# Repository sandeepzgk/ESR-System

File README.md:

## Electrical Stochastic Resonance (ESR) System : Source Code

This repository hosts the full source for an end‑to‑end ESR system:
- A web‑based RC circuit analyzer (Simulator)
- MicroPython firmware for a Pico W/2W audio device (Firmware)
- A KiCad hardware design for the device (PCB)
- A local experiment runner for ABX/QUEST studies (ABXTester)

Hosted analyzer (no install): https://sandeepzgk.github.io/ESR-System/

### Quick links
- Simulator (web analyzer): Simulator/README.md : hosted at https://sandeepzgk.github.io/ESR-System/
- Firmware (Pico W/2W): Firmware/README.md
- PCB (sr‑device KiCad): PCB/README.md
- ABXTester (experiment runner): ABXTester/readme.md

### Repository structure
- Simulator/ : React + TypeScript single‑page app for ESR RC analysis (sine and noise modes), Tailwind UI, GitHub Pages deploy
- Firmware/ : MicroPython code for Wi‑Fi control and I2S audio playback (HTTP endpoints: play/gain/led/status), Q15 volume scaling
- PCB/ : KiCad project (schematic/PCB), repo‑local libraries and production outputs (v1, v2); JLC importer utility
- ABXTester/ : Flask‑based local runner for experiments (QUEST thresholding + ABX trials), CSV/JSON results

### Citations

#### APA
Kollannur, S., Zhao, F., Chen, Y., & Culbertson, H. (2025). Electrical Stochastic Resonance (ESR) System [Computer software]. GitHub. https://github.com/sandeepzgk/ESR-System

#### MLA
Kollannur, S., Zhao, F., Chen, Y., and Culbertson, H. Electrical Stochastic Resonance (ESR) System. 2025. GitHub, https://github.com/sandeepzgk/ESR-System.

#### Chicago
Kollannur, S., F. Zhao, Y. Chen, and H. Culbertson. 2025. Electrical Stochastic Resonance (ESR) System. GitHub repository. https://github.com/sandeepzgk/ESR-System.

#### BibTeX
```bibtex
@software{esr_system_2025,
  author    = {Kollannur, S. and Zhao, F. and Chen, Y. and Culbertson, H.},
  title     = {Electrical Stochastic Resonance (ESR) System},
  year      = {2025},
  publisher = {GitHub},
  url       = {https://github.com/sandeepzgk/ESR-System},
  note      = {A system for electrical stochastic resonance research including circuit analysis, firmware, hardware design, and experiment tools}
}
```

#### Software Citation Format
Kollannur, S., Zhao, F., Chen, Y., & Culbertson, H. (2025). Electrical Stochastic Resonance (ESR) System [Source code]. GitHub. https://github.com/sandeepzgk/ESR-System : A system for electrical stochastic resonance research including circuit analysis, firmware, hardware design, and experiment tools.

### Brief technical summary
- Web analyzer: React 18 + TypeScript, Tailwind; static SPA deployable to GitHub Pages
- Firmware: MicroPython on RP2040 (Pico W/2W), machine.I2S TX, HTTP API over Wi‑Fi
- Hardware: KiCad project with pinned repo‑local symbol/footprint/3D libraries; production files for fabrication
- Experiments: Python (Flask) with two‑channel audio playback, CSV/JSON logging, QUEST thresholding

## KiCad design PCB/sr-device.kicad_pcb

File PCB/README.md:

## PCB SR Device KiCad Project

### 1) Overview
KiCad project for the ESR hardware: a Pico‑based audio playback/amp board ("sr-device"). Includes:
- KiCad schematic, PCB, and project files (sr-device.kicad_*)
- Curated symbol/footprint/3D libraries under PCB/lib for key parts (DAC, amplifier, regulators, passives, connectors)
- Production outputs under PCB/production/v1 and v2 (BOM, positions, designators, zipped fab packages)
- jlcimporter.py utility to generate and normalize part libraries using JLC2KiCadLib

Notable parts
- DAC: PCM5100A
- Amplifier: TPA3112D1
- Regulators: LM78M05C, LM7812S, LM1085IS-12, AP7333-33
- Inductors/caps/resistors; Pico headers/footprints; custom logos

### 2) How to open / produce outputs
Open in KiCad 7/8
- Open PCB/sr-device.kicad_pro; KiCad will resolve sym-lib-table and fp-lib-table to PCB/lib/*

Generate fabrication
- Use KiCad’s Plot and Fabrication Toolkit (options in fabrication-toolkit-options.json)
- Export Gerbers, drill files, position files, and BOM as needed

JLC integration workflow
- jlcimporter.py wraps JLC2KiCadLib to create per‑part libraries under PCB/lib/<MFR_PART>/
- It normalizes filenames (symbol.kicad_sym, footprint.kicad_mod, model.step) and updates lib tables
- Run from PCB/: python jlcimporter.py --lcsc_part_numbers C12345 C67890

### 3) Where it has been tested
- Designed and opened in KiCad; produced v1 and v2 outputs in PCB/production
- Libraries resolved via sym-lib-table and fp-lib-table within this project (KIPRJMOD relative paths)

### 4) History and rationale (commit highlights)
- 79621ca (PCB): Initial KiCad project checked in with curated libraries and production artifacts (v1, v2)
- Custom library structure chosen for reproducibility and to avoid external dependency drift; jlcimporter.py automates bringing JLC parts into repo‑local libs

Design choices
- Repo‑local symbol/footprint/3D models for repeatable builds and offline use
- KIPRJMOD‑relative paths in lib tables so the project remains portable
- Versioned production output directories to track released fab packages

### 5) Brief technical summary
- EDA: KiCad project with sym/fp tables pinned to PCB/lib
- Manufacturing: BOM/pos/designator exports for JLC; STEP models included for 3D
- Utilities: Python importer normalizes JLC outputs and patches lib tables

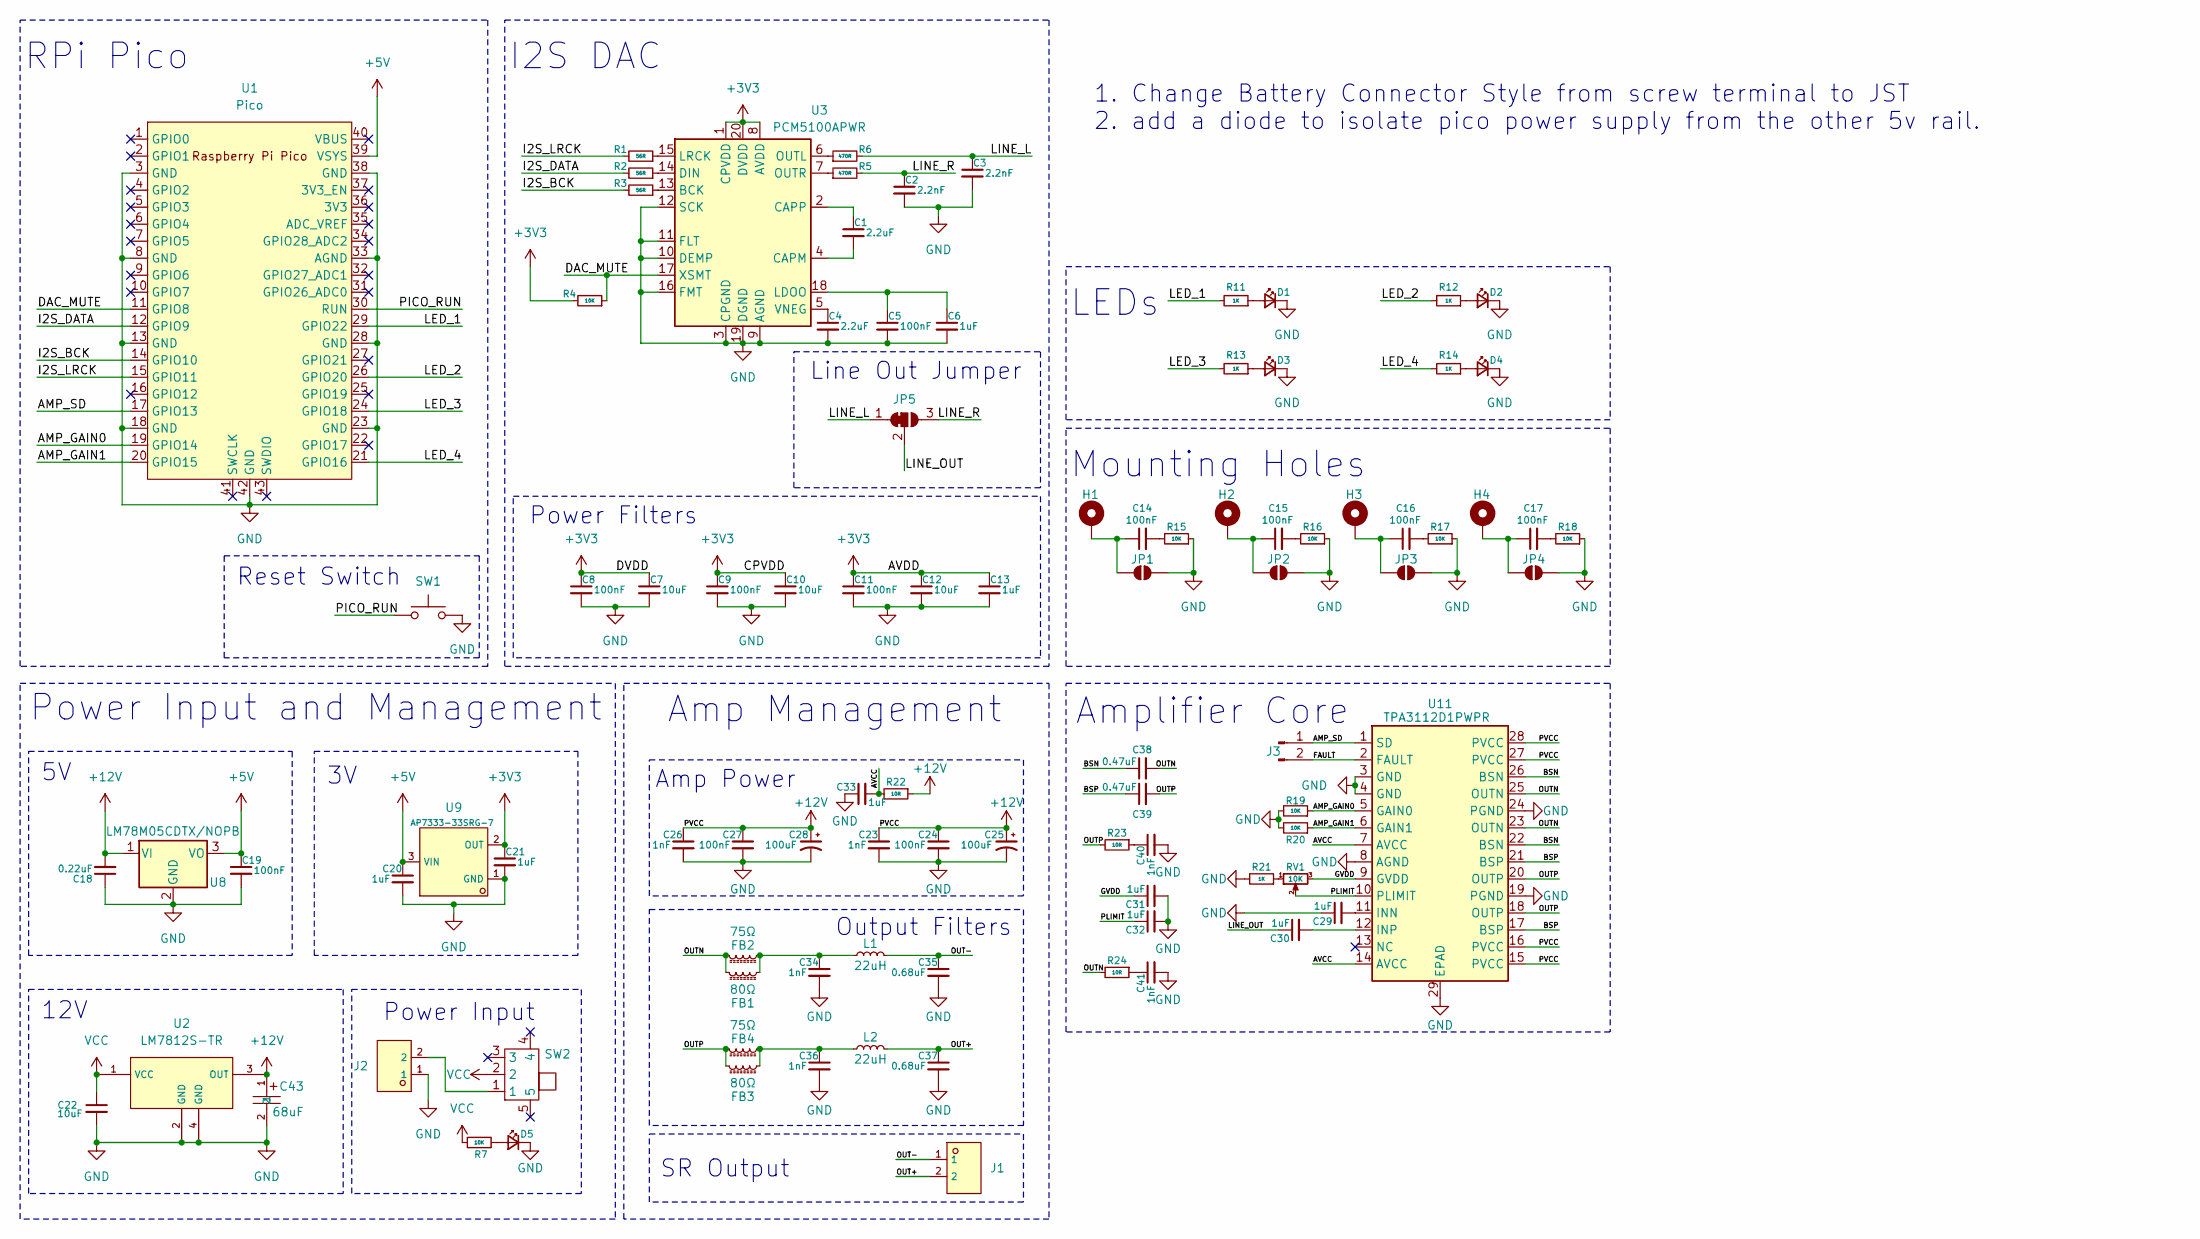
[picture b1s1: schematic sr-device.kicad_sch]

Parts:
C1, C4: 2.2uF; C_0603_1608Metric; LCSC C57895
C2, C3: 2.2nF; C_0603_1608Metric; LCSC C2835509
C5, C8, C9, C11, C14, C15, C16, C17, C19, C24, C27: 100nF; C_0603_1608Metric; LCSC C88219
C6, C13, C20, C21, C29, C30, C31, C32, C33: 1uF; C_0603_1608Metric; LCSC C841050
C7, C10, C12, C22: 10uF; C_0603_1608Metric; LCSC C386081
C18: 0.22uF; C_0603_1608Metric; LCSC C107083
C23, C26, C34, C36, C40, C41: 1nF; C_0603_1608Metric; LCSC C340644
C25, C28: 100uF; CP_Elec_6.3x5.4; LCSC C2887272
C35, C37: 0.68uF; C_0603_1608Metric; LCSC C694504
C38, C39: 0.47uF; C_0603_1608Metric; LCSC C162281
C43: 68uF; footprint; LCSC C7220
D1, D2, D3, D4, D5: LED_Small; LED_0603_1608Metric; LCSC C89811
FB1, FB3: 80Ω; L_0805_2012Metric; LCSC C2971887
FB2, FB4: 75Ω; L_1806_4516Metric; LCSC C14586
H1, H2, H3, H4: MountingHole; MountingHole_3.2mm_M3_ISO7380_Pad
J1, J2: KF301-5_0-2P; footprint; LCSC C474881
J3: Conn_01x02_Pin; PinHeader_1x02_P2.54mm_Vertical; LCSC DNP
JP1, JP2, JP3, JP4: SolderJumper_2_Open; SolderJumper-2_P1.3mm_Open_TrianglePad1.0x1.5mm
JP5: SolderJumper_3_Bridged12; SolderJumper-3_P1.3mm_Bridged12_RoundedPad1.0x1.5mm
L1, L2: 22uH; footprint; LCSC C845053
R1, R2, R3: 56R; R_0603_1608Metric; LCSC C227967
R4, R7, R15, R16, R17, R18, R19, R20: 10K; R_0603_1608Metric; LCSC C465463
R5, R6: 470R; R_0603_1608Metric; LCSC C114669
R11, R12, R13, R14, R21: 1K; R_0603_1608Metric; LCSC C73797
R22, R23, R24: 10R; R_0603_1608Metric; LCSC C441910
RV1: 10K; footprint; LCSC C515300
SW1: PTS636SK25SMTRLFS; footprint; LCSC C2689642
SW2: SS-12D11L7; LCSC C2884775
U1: Pico; RPi_Pico_SMD_TH
U2: LM7812S-TR; footprint; LCSC C507140
U3: PCM5100APWR; TSSOP-20_4.4x6.5mm_P0.65mm; LCSC C131154
U8: LM78M05CDTX/NOPB; footprint; LCSC C544492
U9: AP7333-33SRG-7; footprint; LCSC C150745
U11: TPA3112D1PWPR; footprint; LCSC C133544

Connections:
+3V3: C7.1, C8.1, C9.1, C10.1, C11.1, C12.1, C13.1, C21.1, R4.2, U3.1 (CPVDD), U3.8 (AVDD), U3.20 (DVDD), U9.2 (OUT)
+5V: C19.1, C20.1, U1.39 (VSYS), U8.3 (VO), U9.3 (VIN)
+12V: C18.2, C23.1, C24.1, C25.1, C26.1, C27.1, C28.1, C43.1, R22.1, U2.3 (OUT), U8.1 (VI), U11.15 (PVCC), U11.16 (PVCC), U11.27 (PVCC), U11.28 (PVCC)
/AMP_GAIN0: R19.1, U1.19 (GPIO14), U11.5 (GAIN0)
/AMP_GAIN1: R20.1, U1.20 (GPIO15), U11.6 (GAIN1)
/AMP_SD: J3.1, U1.17 (GPIO13), U11.1 (SD)
/AVCC: C33.2, R22.2, U11.7 (AVCC), U11.14 (AVCC)
/BSN: C38.1, U11.22 (BSN), U11.26 (BSN)
/BSP: C39.1, U11.17 (BSP), U11.21 (BSP)
/DAC_MUTE: R4.1, U1.11 (GPIO8), U3.17 (XSMT)
/FAULT: J3.2, U11.2 (FAULT)
/GVDD: C31.1, RV1.3, U11.9 (GVDD)
/I2S_BCK: R3.2, U1.14 (GPIO10)
/I2S_DATA: R2.2, U1.12 (GPIO9)
/I2S_LRCK: R1.2, U1.15 (GPIO11)
/LED_1: R11.2, U1.29 (GPIO22)
/LED_2: R12.2, U1.26 (GPIO20)
/LED_3: R13.2, U1.24 (GPIO18)
/LED_4: R14.2, U1.21 (GPIO16)
/LINE_L: C3.1, JP5.1 (A), R6.2
/LINE_OUT: C30.1, JP5.2 (C)
/LINE_R: C2.1, JP5.3 (B), R5.2
/OUT+: C37.1, J1.2, L2.1
/OUT-: C35.1, J1.1, L1.1
/OUTN: C38.2, FB1.2, FB2.2, R24.2, U11.23 (OUTN), U11.25 (OUTN)
/OUTP: C39.2, FB3.2, FB4.2, R23.2, U11.18 (OUTP), U11.20 (OUTP)
/PICO_RUN: SW1.1, U1.30 (RUN)
/PLIMIT: C32.1, RV1.2, U11.10 (PLIMIT)
GND: C2.2, C3.2, C4.2, C5.2, C6.2, C7.2, C8.2, C9.2, C10.2, C11.2, C12.2, C13.2, C18.1, C19.2, C20.2, C21.2, C22.2, C23.2, C24.2, C25.2, C26.2, C27.2, C28.2, C29.1, C31.2, C32.2, C33.1, C34.2, C35.2, C36.2, C37.2, C40.2, C41.2, C43.2, D1.1 (K), D2.1 (K), D3.1 (K), D4.1 (K), D5.1 (K), J2.1, JP1.2 (B), JP2.2 (B), JP3.2 (B), JP4.2 (B), R15.1, R16.1, R17.1, R18.1, R19.2, R20.2, R21.2, SW1.2, U1.3 (GND), U1.8 (GND), U1.13 (GND), U1.18 (GND), U1.23 (GND), U1.28 (GND), U1.33 (AGND), U1.38 (GND), U1.42 (GND), U2.2 (GND), U2.4 (GND), U3.3 (CPGND), U3.9 (AGND), U3.10 (DEMP), U3.11 (FLT), U3.12 (SCK), U3.16 (FMT), U3.19 (DGND), U8.2 (GND), U9.1 (GND), U11.3 (GND), U11.4 (GND), U11.8 (AGND), U11.19 (PGND), U11.24 (PGND), U11.29 (EPAD)
unnamed: C14.2, R15.2
unnamed: C15.2, R16.2
unnamed: C16.2, R17.2
unnamed: C17.2, R18.2
unnamed: C34.1, FB1.1, FB2.1, L1.2
unnamed: C36.1, FB3.1, FB4.1, L2.2
unnamed: C40.1, R23.1
unnamed: C41.1, R24.1
unnamed: D1.2 (A), R11.1
unnamed: D2.2 (A), R12.1
unnamed: D3.2 (A), R13.1
unnamed: D4.2 (A), R14.1
unnamed: D5.2 (A), R7.1
unnamed: J2.2, SW2.1
unnamed: C14.1, H1.1, JP1.1 (A)
unnamed: C15.1, H2.1, JP2.1 (A)
unnamed: C16.1, H3.1, JP3.1 (A)
unnamed: C17.1, H4.1, JP4.1 (A)
unnamed: R21.1, RV1.1
unnamed: R3.1, U3.13 (BCK)
unnamed: C1.2, U3.4 (CAPM)
unnamed: C1.1, U3.2 (CAPP)
unnamed: R2.1, U3.14 (DIN)
unnamed: C5.1, C6.1, U3.18 (LDOO)
unnamed: R1.1, U3.15 (LRCK)
unnamed: R6.1, U3.6 (OUTL)
unnamed: R5.1, U3.7 (OUTR)
unnamed: C4.1, U3.5 (VNEG)
unnamed: C29.2, U11.11 (INN)
unnamed: C30.2, U11.12 (INP)
VCC: C22.1, R7.2, SW2.2, U2.1 (VCC)

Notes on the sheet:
Mounting Holes
RPi Pico
Power Filters
1. Change Battery Connector Style from screw terminal to JST 2. add a diode to isolate pico power supply from the other 5v rail.
Power Input and Management
LEDs
Amp Management
SR Output
Output Filters
I2S DAC
Line Out Jumper
Reset Switch
Amplifier Core
12V
Amp Power
Power Input

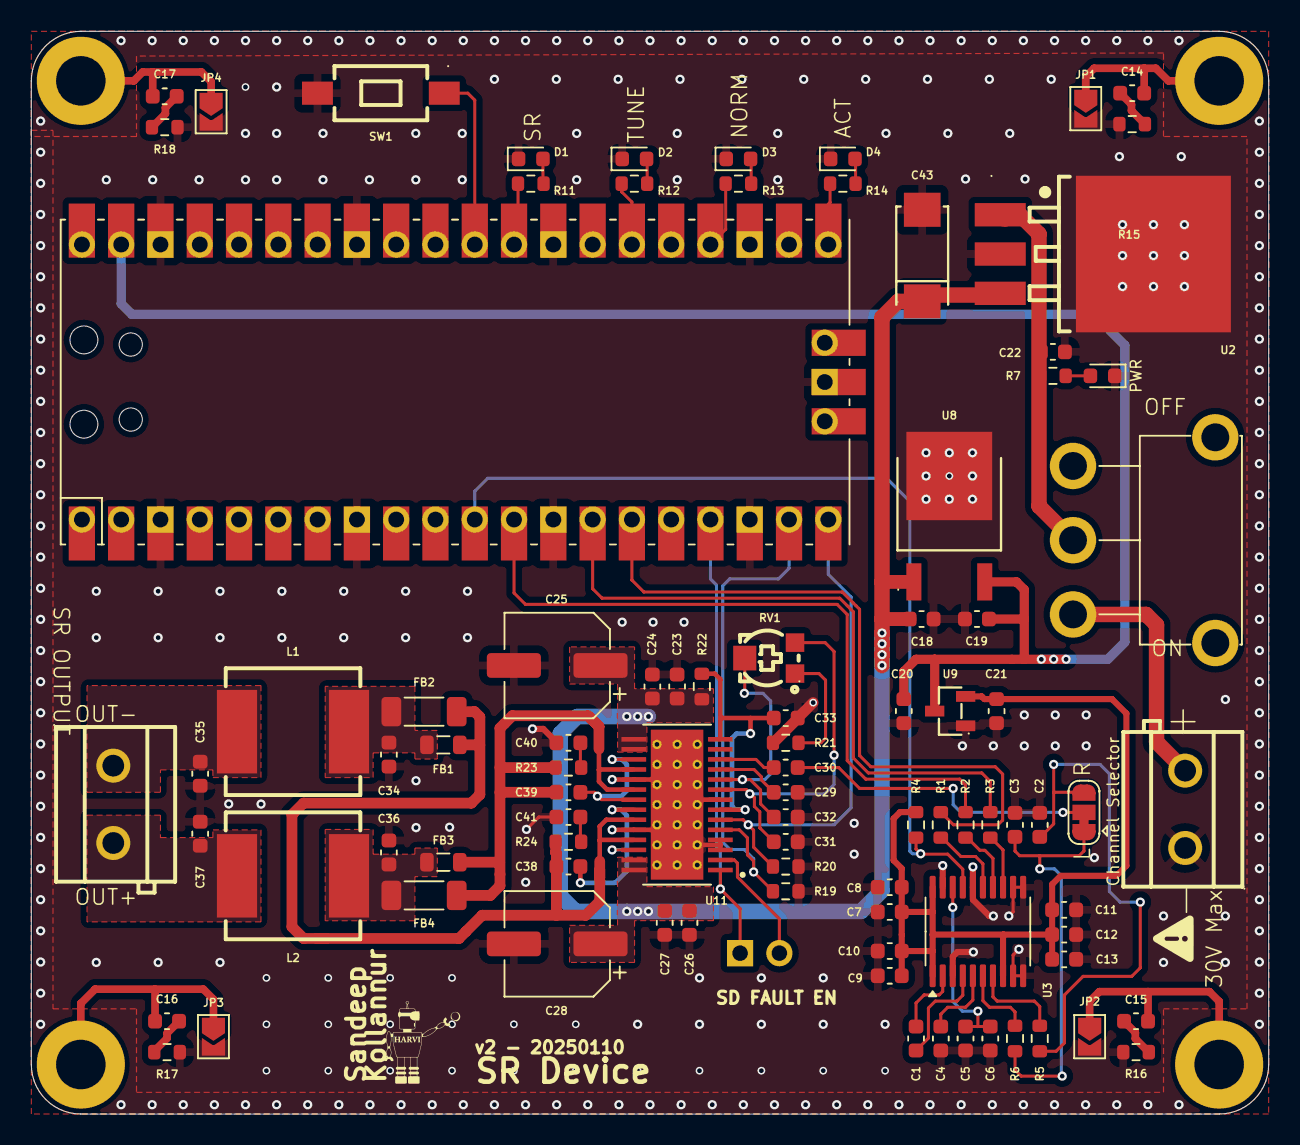
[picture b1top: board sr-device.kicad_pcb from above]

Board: 2 copper layers, 80.0 x 70.0 mm, 95 parts (1 on the bottom side), 60 nets.

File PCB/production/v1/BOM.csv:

Designator,Footprint,Quantity,Value,LCSC Part #
"C1, C2, C3, C4",Capacitor_SMD:C_0603_1608Metric,4,2.2nF,C2835509
"C10, C12, C22, C7",Capacitor_SMD:C_0603_1608Metric,4,10uF,C386081
"C11, C14, C15, C16, C17, C19, C24, C27, C5, C8, C9",Capacitor_SMD:C_0603_1608Metric,11,100nF,C88219
"C13, C20, C21, C29, C30, C31, C32, C33, C40, C41, C6",Capacitor_SMD:C_0603_1608Metric,11,1uF,C841050
C18,Capacitor_SMD:C_0603_1608Metric,1,0.22uF,C107083
"C23, C26, C34, C36",Capacitor_SMD:C_0603_1608Metric,4,1nF,C340644
"C25, C28",Capacitor_SMD:CP_Elec_6.3x5.4,2,100uF,C2887272
"C35, C37",Capacitor_SMD:C_0603_1608Metric,2,0.68uF,C694504
"C38, C39",Capacitor_SMD:C_0603_1608Metric,2,0.47uF,C162281
C43,TAJC686K016RNJ,1,68uF,C7220
"D1, D2, D3, D4, D5",LED_SMD:LED_0603_1608Metric,5,LED_Small,C89811
"FB1, FB3",Inductor_SMD:L_0805_2012Metric,2,80Ω,C2971887
"FB2, FB4",Inductor_SMD:L_1806_4516Metric,2,75Ω,C14586
"J1, J2",KF301-5_0-2P,2,KF301-5_0-2P,C474881
"L1, L2",IHLP3232DZER220M11,2,22uH,C845053
"R1, R2, R3",Resistor_SMD:R_0603_1608Metric,3,56R,C227967
"R11, R12, R13, R14, R21",Resistor_SMD:R_0603_1608Metric,5,1K,C73797
"R15, R16, R17, R18, R19, R20, R4, R7",Resistor_SMD:R_0603_1608Metric,8,10K,C465463
"R22, R23, R24",Resistor_SMD:R_0603_1608Metric,3,10R,C441910
"R5, R6",Resistor_SMD:R_0603_1608Metric,2,470R,C114669
RV1,VG039NSNXTB103,1,"10K, replacement for out of stock C719176",C719176
SW1,PTS636SK25SMTRLFS,1,PTS636SK25SMTRLFS,C2689642
SW2,SS-12D11L7:SS-12D11L7,1,SS-12D11L7,C2884775
U1,RPi_Pico_SMD_TH,1,Pico,DNP
U10,LM1085IS-12-NOPB,1,LM1085IS-12/NOPB,C130908
U11,TPA3112D1PWPR,1,TPA3112D1PWPR,C133544
U3,Package_SO:TSSOP-20_4.4x6.5mm_P0.65mm,1,PCM5100APWR,C131154
U8,LM78M05CDTX-NOPB,1,LM78M05CDTX/NOPB,C544492
U9,AP7333-33SRG-7,1,AP7333-33SRG-7,C150745

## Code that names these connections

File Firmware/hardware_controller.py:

from machine import Pin, I2S
import time, gc
import micropython

# --------------------
# fixed‑point scaler: in-place scale of signed 16‑bit samples
# scale a bytearray in-place, sample‑wise, with fixed-point Q15 volume
@micropython.viper
def _viper_scale16(buf: ptr8, n: int, vol_q15: int):
    i = int(0)
    # n = number of 16‑bit samples; buf is ptr8 to bytes
    while i < n:
        off = i * 2
        lo = buf[off]              # low byte
        hi = buf[off + 1]          # high byte
        raw = lo | (hi << 8)       # assemble little‑endian word
        # signed conversion
        if raw & 0x8000:
            s = raw - 0x10000
        else:
            s = raw
        # Q15 scale
        s = (s * vol_q15) >> 15
        # clamp
        if s < -32768:
            s = -32768
        elif s > 32767:
            s = 32767
        # write back
        v = s & 0xFFFF
        buf[off]     = v & 0xFF
        buf[off + 1] = (v >> 8) & 0xFF
        i += 1


# --------------------

class HardwareController:    
    def __init__(self, config):
        self.config = config
        self.audio = config["audio"]
        self.led = Pin(config["pins"]["led"], Pin.OUT)
        self.i2s = None

        self.dac_mute = Pin(config["pins"]["mute"], Pin.OUT)
        self.amp_gain0 = Pin(config["pins"]["amp_gain0"], Pin.OUT)
        self.amp_gain1 = Pin(config["pins"]["amp_gain1"], Pin.OUT)
        self.amp_sd = Pin(config["pins"]["amp_sd"], Pin.OUT)

    def blink_led(self, count):
        for _ in range(count):
            self.led.on()
            time.sleep(0.2)
            self.led.off()
            time.sleep(0.2)

    def enable_audio(self):
        """Enable audio output by unmuting DAC and enabling amplifier."""
        self.dac_mute.value(1)
        self.amp_sd.value(1)
        print("DAC and amplifier enabled")  

    def disable_audio(self):
        """Disable audio output by muting DAC and disabling amplifier."""
        self.dac_mute.value(0)
        self.amp_sd.value(0)
        print("DAC and amplifier disabled")

    def set_gain(self, gain_level):
        """
        Set amplifier gain level.
        gain_level: 0-3 (0: +20dB, 1: +26dB, 2: +32dB, 3: +36dB)
        """
        if gain_level < 0 or gain_level > 3:
            raise ValueError("Gain level must be between 0 and 3")
        self.amp_gain0.value(gain_level & 0x01)
        self.amp_gain1.value((gain_level >> 1) & 0x01)
        print(f"Amplifier gain set to level {gain_level}")        

    def initialize_i2s(self):
        """
        Initialize I2S interface with a DMA buffer sized in bytes.
        Uses 'dma_buffer_frames' (or falls back to 'buffer_length') and
        the pins from self.config["pins"].
        """
        # bytes per stereo frame = (bits per sample / 8) × 2 channels
        frame_size = (self.audio["bits_per_sample"] // 8) * 2

        # pick dma_buffer_frames if present, else buffer_length
        dma_frames = self.audio.get("dma_buffer_frames", self.audio["buffer_length"])
        ibuf_size = dma_frames * frame_size

        print(f"Initializing I2S: Using DMA buffer frames = {dma_frames} (ibuf = {ibuf_size} bytes)")

        pins = self.config["pins"]
        # id=0 must be passed positionally; pins come in as keywords
        self.i2s = I2S(
            0,                           # I2S peripheral ID as positional
            sck=Pin(pins["bck"]),        # BCK (bit clock)
            ws=Pin(pins["lrck"]),        # LRCK / WS (word select)
            sd=Pin(pins["data"]),        # SD (serial data)
            mode=I2S.TX,
            bits=self.audio["bits_per_sample"],
            format=I2S.STEREO,
            rate=self.audio["sample_rate"],
            ibuf=ibuf_size
        )


    def play_audio(self,
                   wave_generator,
                   playback_frames=None,
                   aggregate_count=16,
                   debug=False,
                   duration_seconds=None,
                   volume: float = 1.0):
        """
        volume: float in [0.0, 1.0]
        """
        import gc, time

        # pre‑compute integer Q15 volume
        vol_q15 = int(volume * 32767)

        # 1) determine frames per write
        if playback_frames is None:
            playback_frames = self.audio.get(
                "playback_frames",
                self.audio["buffer_length"]
            )

        # 2) init I2S if needed
        if self.i2s is None:
            self.initialize_i2s()

        # 3) free memory & enable audio
        gc.collect()
        self.enable_audio()

        # 4) fixed‑duration?
        if duration_seconds is not None:
            duration_ms = int(duration_seconds * 1000)
            start_ms = time.ticks_ms()

        # 5) pre‑fill 4 buffers
        for i in range(4):
            # always get a fresh bytearray so we can mutate it
            raw = wave_generator.generate_buffer(playback_frames)
            buf = bytearray(raw)
            if vol_q15 != 32767:
                _viper_scale16(buf, len(buf) // 2, vol_q15)
            written = self.i2s.write(buf)
            if debug:
                print(f"[DEBUG] Pre‑fill #{i+1}: wrote {written}/{len(buf)} bytes")

        last_loop = time.ticks_ms()
        write_count = 0
        total_dt    = 0

        print(f"Starting audio output{' for '+str(duration_seconds)+'s' if duration_seconds else ''}...")
        try:
            while (duration_seconds is None or
                   time.ticks_diff(time.ticks_ms(), start_ms) < duration_ms):

                ws = time.ticks_ms()

                # pull & scale each chunk
                raw = wave_generator.generate_buffer(playback_frames)
                buf = bytearray(raw)
                if vol_q15 != 32767:
                    _viper_scale16(buf, len(buf) // 2, vol_q15)

                written = self.i2s.write(buf)
                we = time.ticks_ms()
                dt  = time.ticks_diff(we, ws)
                gap = time.ticks_diff(we, last_loop)
                last_loop = we
                write_count += 1
                total_dt   += dt

                if debug:
                    print(f"[DIAG] Write#{write_count}: dt={dt}ms, gap={gap}ms, "
                        f"bytes={written}, free={gc.mem_free()}")

                # if I2S didn’t accept the full buffer, give it a moment
                expected = (aggregate_count
                            * playback_frames
                            * ((self.audio['bits_per_sample'] // 8) * 2))
                if written < expected:
                    if debug:
                        print("[DIAG] Incomplete write → sleep 5 ms")
                    time.sleep_ms(2)

                # every 100 writes, print the average
                if write_count % 100 == 0:
                    avg = total_dt / write_count
                    print(f"[DIAG] Avg write over {write_count} cycles: {avg:.2f} ms")

                if gc.mem_free() < 10000:
                    gc.collect()

        except KeyboardInterrupt:
            print("Audio playback interrupted by user")
        except Exception as e:
            print(f"Error during audio playback: {e}")
        finally:
            self.disable_audio()

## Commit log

2025-04-25 Simulator
2025-04-25 Firmware
2025-04-25 ABXTester
2025-04-25 working launch with local tailwind
2025-04-25 Adding units and minor ui changes
2025-04-26 wip with animation
2025-04-28 fixed typescript errors, and modularizaing
2025-04-28 moduliarized
2025-04-28 updated frrequency chart
2025-04-29 noise v1
2025-04-29 hidpi support
2025-04-29 hidpi fix
2025-04-29 removing the old code
2025-04-29 16:9 ratio dashboardification
2025-04-29 working 16:9 version with bugs
2025-04-29 proper log scale fix
2025-04-29 sliders
2025-04-29 somewhatworkign dual slider
2025-04-29 finally working
2025-04-29 better defaults
2025-04-29 resolution check
2025-04-29 validation
2025-04-30 with circuit diagram
2025-04-30 github deploy
2025-04-30 moving actions to root
2025-04-30 removed cache config to hopefully build now
2025-04-30 removed eslint erroring
2025-04-30 image fixes
2025-04-30 reworking image location to use process.env
2025-05-05 additional misc firmware tools
2025-05-05 fixes for equations
2025-05-05 mobile setup
2025-05-05 refactoring math
2025-05-06 restoring old notes
2025-05-06 integration approach for wrc calculation for noise
2025-09-01 changed to ESR system
2025-09-01 Add comprehensive README files for all modules
    Introduced detailed README.md files for ABXTester, Firmware, PCB, Simulator, and the repository root. These documents provide overviews, setup instructions, technical summaries, and rationale for eac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
2025-09-01 Rename safety threshold to user specified threshold
    Updated all references from 'Safety Threshold' to 'User Specified Safety Threshold' for clarity in UI, documentation, and code comments. Added references and model description to README and results i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
2025-09-01 Create LICENSE
